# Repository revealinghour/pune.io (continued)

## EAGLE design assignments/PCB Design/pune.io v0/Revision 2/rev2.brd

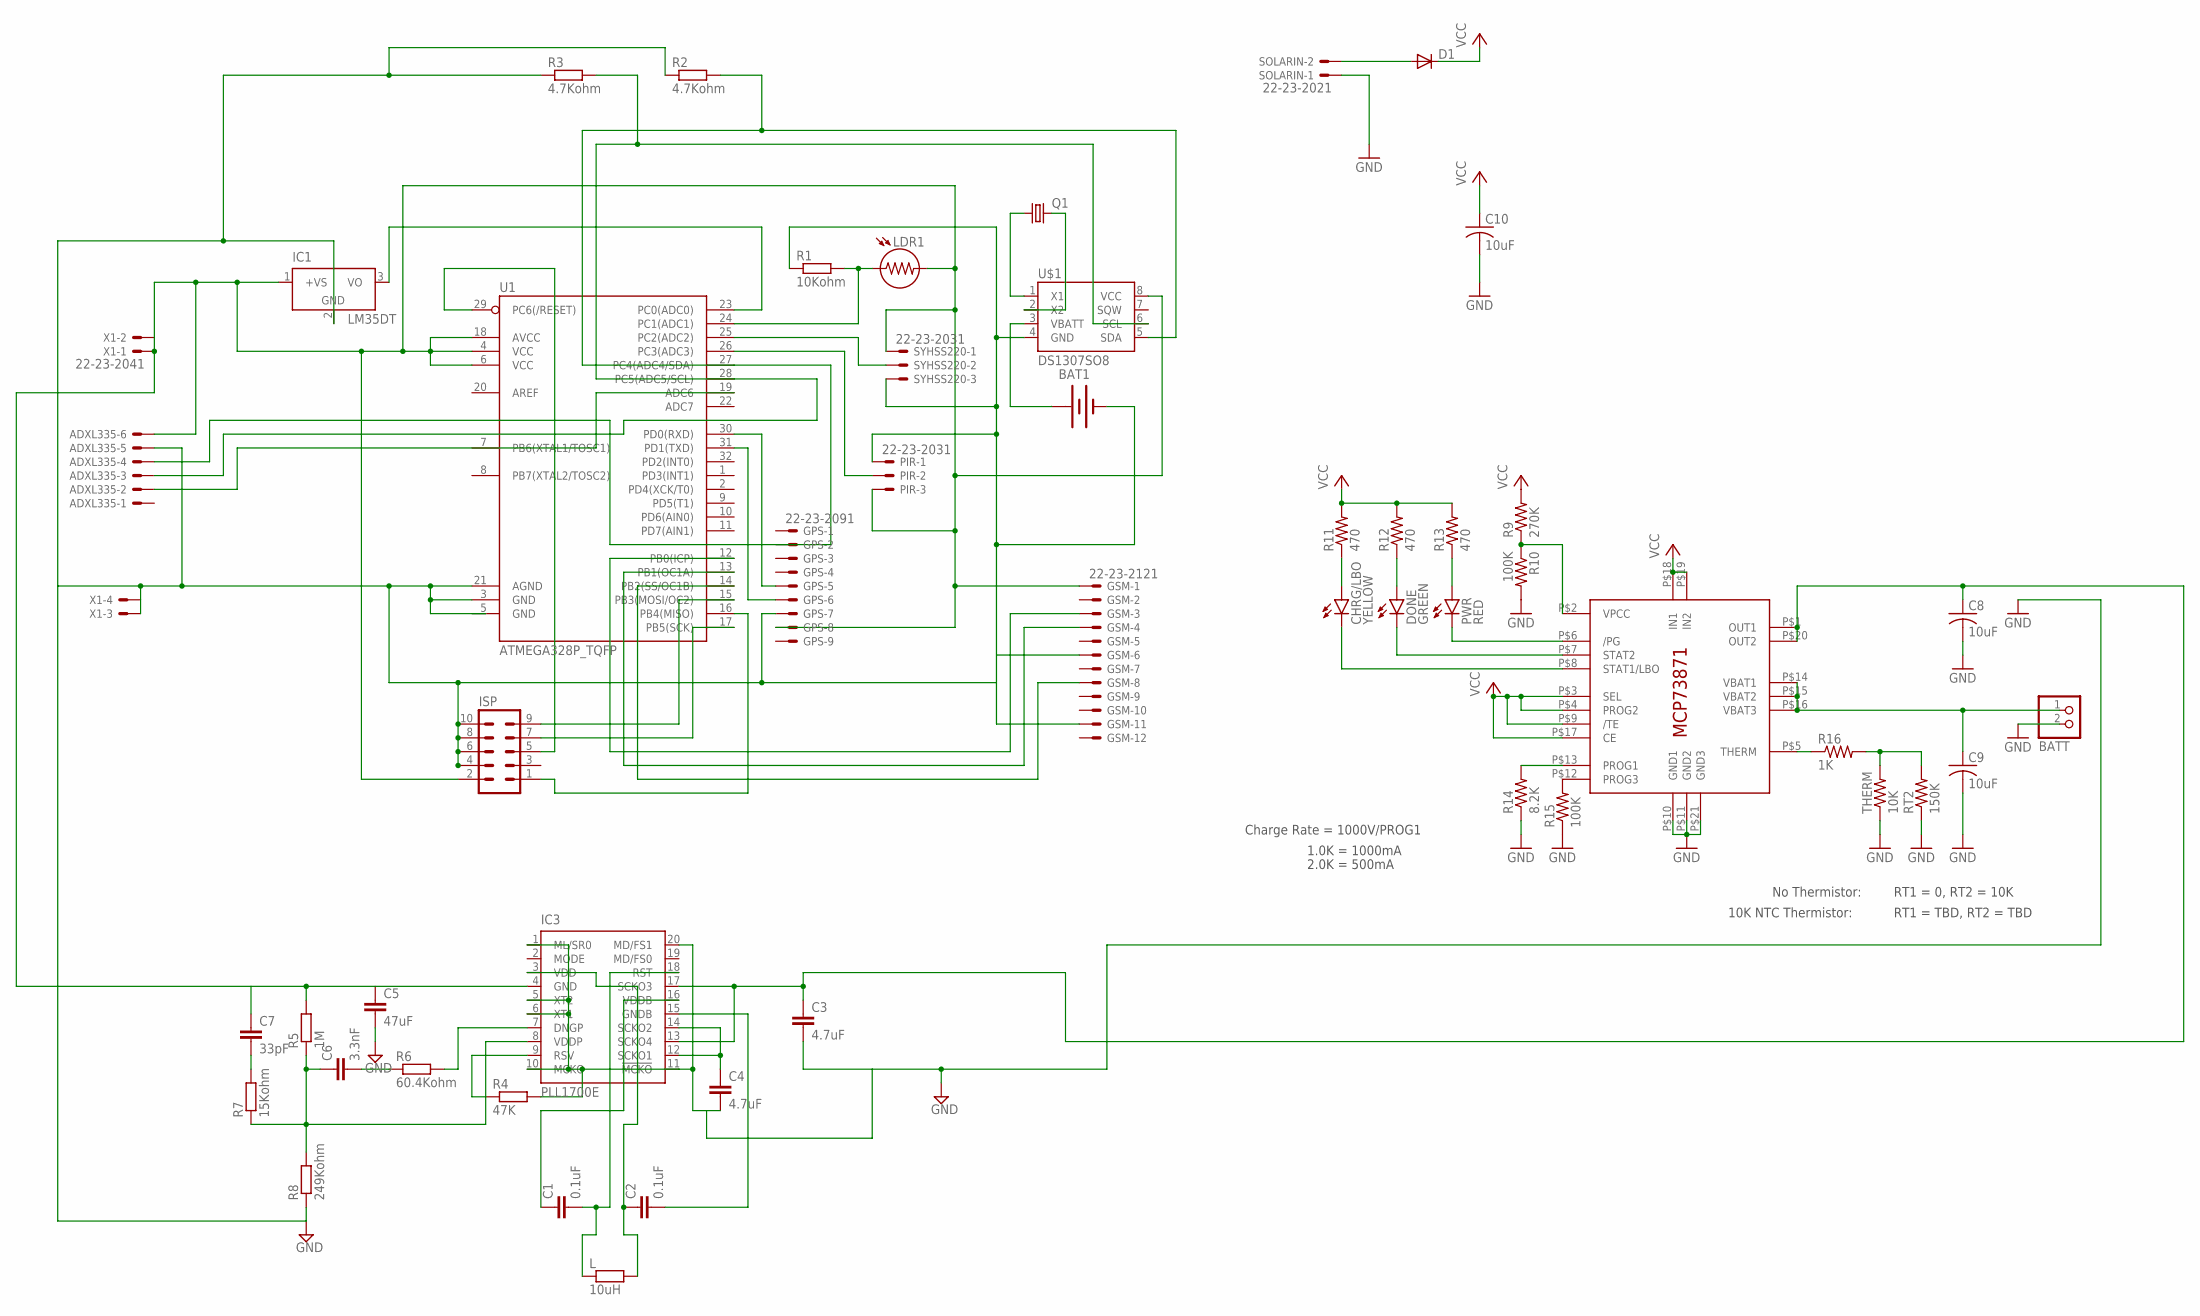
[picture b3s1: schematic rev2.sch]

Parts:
ADXL335: 22-23-2061
BAT1: BATTERY20PTH; BATTCOM_20MM_PTH
BATT: JST_2PIN-SMT-RA; JST-PH-2-SMT-RA
C1, C2: 0.1uF; 0402-CAP
C3, C4: 4.7uF; 0603-CAP
C5: 47uF; 0603-CAP
C6: 3.3nF; 0603-CAP
C7: 33pF; 0603-CAP
C8, C9, C10: 10uF; C0805K
CHRG/LBO: YELLOW; LED-1206
D1: DIODEPTH; DIODE-1N4001
DONE: GREEN; LED-1206
GPS: 22-23-2091
GSM: 22-23-2121
IC1: LM35DT; TO220V
IC2: MCP73871; QFN20_4MM
IC3: PLL1700E; SSOP20
ISP: ML10
L: 10uH; R0207/4
LDR1: LDR5MM; LDR338-54C
PIR: 22-23-2031
PWR: RED; LED-1206
Q1: CRYSTALTC26H; TC26H
R1: 10Kohm; M1206
R2, R3: 4.7Kohm; M1206
R4: 47K; M3216
R5: 1M; M3216
R6: 60.4Kohm; M3216
R7: 15Kohm; M1206
R8: 249Kohm; M1206
R9: 270K; R0805
R10, R15: 100K; R0805
R11, R12, R13: 470; 0603-RES
R14: 8.2K; 0603-RES
R16: 1K; M0805
RT2: 150K; M0805
SOLARIN: 22-23-2021
SYHSS220: 22-23-2031
THERM: 10K; 0805-THM
U1: ATMEGA328P_TQFP; TQFP32-08
U$1: DS1307SO8; SO08
X1: 22-23-2041

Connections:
BATT: BATT.1 (2), C9.1, IC2.P$14 (VBAT1), IC2.P$15 (VBAT2), IC2.P$16 (VBAT3)
GND: ADXL335.5, BAT1.2 (-), BATT.2 (1), C3.2, C4.2, C5.2, C8.2, C9.2, C10.2, GPS.7, GSM.6, GSM.11, IC1.2 (GND), IC2.P$10 (GND1), IC2.P$11 (GND2), IC2.P$21 (GND3), IC3.1 (ML/SR0), IC3.5 (XT2), IC3.6 (XT1), IC3.10 (MCKO), IC3.11 (!MCKO), IC3.20 (MD/FS1), ISP.4, ISP.6, ISP.8, ISP.10, PIR.1, R1.1, R2.1, R3.1, R4.2, R8.1, R10.2, R14.1, R15.1, RT2.1, SOLARIN.1, SYHSS220.3, THERM.1, U1.3 (GND), U1.21 (AGND), U$1.4 (GND), X1.3, X1.4
unnamed: GPS.5, U1.30 (PD0(RXD))
unnamed: IC1.3 (VO), U1.23 (PC0(ADC0))
unnamed: LDR1.1, R1.2, U1.24 (PC1(ADC1))
unnamed: GPS.6, U1.31 (PD1(TXD))
unnamed: SYHSS220.2, U1.25 (PC2(ADC2))
unnamed: PIR.2, U1.26 (PC3(ADC3))
unnamed: ADXL335.2, U1.19 (ADC6)
unnamed: ADXL335.3, R3.2, U1.28 (PC5(ADC5/SCL)), U$1.6 (SCL)
unnamed: GSM.3, U1.12 (PB0(ICP))
unnamed: Q1.1, U$1.1 (X1)
unnamed: Q1.2, U$1.2 (X2)
unnamed: GSM.4, U1.13 (PB1(OC1A))
unnamed: BAT1.1 (+), U$1.3 (VBATT)
unnamed: GSM.8, U1.14 (PB2(SS/OC1B))
unnamed: IC2.P$2 (VPCC), R9.1, R10.1
unnamed: IC2.P$6 (/PG), PWR.C
unnamed: ISP.1, U1.16 (PB4(MISO))
unnamed: ISP.5, U1.29 (PC6(/RESET))
unnamed: ISP.7, U1.17 (PB5(SCK))
unnamed: ISP.9, U1.15 (PB3(MOSI/OC2))
unnamed: DONE.C, IC2.P$7 (STAT2)
unnamed: CHRG/LBO.C, IC2.P$8 (STAT1/LBO)
unnamed: C1.1, IC3.16 (VDDB)
unnamed: CHRG/LBO.A, R11.1
unnamed: DONE.A, R12.1
unnamed: C2.2, IC3.15 (GNDB)
unnamed: PWR.A, R13.1
unnamed: IC2.P$12 (PROG3), R15.2
unnamed: C1.2, IC3.18 (RST), L.1
unnamed: C2.1, IC3.3 (VDD), L.2
unnamed: ADXL335.6, C5.1, C7.1, GPS.8, GSM.1, IC1.1 (+VS), IC3.4 (GND), ISP.2, LDR1.2, PIR.3, R5.2, SYHSS220.1, U1.4 (VCC), U1.6 (VCC), U1.18 (AVCC), U$1.8 (VCC), X1.1, X1.2
unnamed: C6.1, IC3.8 (VDDP), R5.1, R7.1, R8.2
unnamed: C6.2, R6.1
unnamed: IC3.7 (DNGP), R6.2
unnamed: ADXL335.4, R2.2, U1.27 (PC4(ADC4/SDA)), U$1.5 (SDA)
unnamed: C7.2, R7.2
unnamed: C4.1, IC3.12 (SCKO1), IC3.14 (SCKO2)
unnamed: IC3.9 (RSV), R4.1
unnamed: IC2.P$13 (PROG1), R14.2
unnamed: IC2.P$5 (THERM), R16.1
unnamed: R16.2, RT2.2, THERM.2
unnamed: D1.A, SOLARIN.2
OUT: C3.1, C8.1, IC2.P$1 (OUT1), IC2.P$20 (OUT2), IC3.13 (SCKO4), IC3.17 (SCKO3)
VCC: C10.1, D1.C, IC2.P$3 (SEL), IC2.P$4 (PROG2), IC2.P$9 (/TE), IC2.P$17 (CE), IC2.P$18 (IN1), IC2.P$19 (IN2), R9.2, R11.2, R12.2, R13.2

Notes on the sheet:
Charge Rate = 1000V/PROG1
1.0K = 1000mA
2.0K = 500mA
No Thermistor:
10K NTC Thermistor:
RT1 = 0, RT2 = 10K
RT1 = TBD, RT2 = TBD

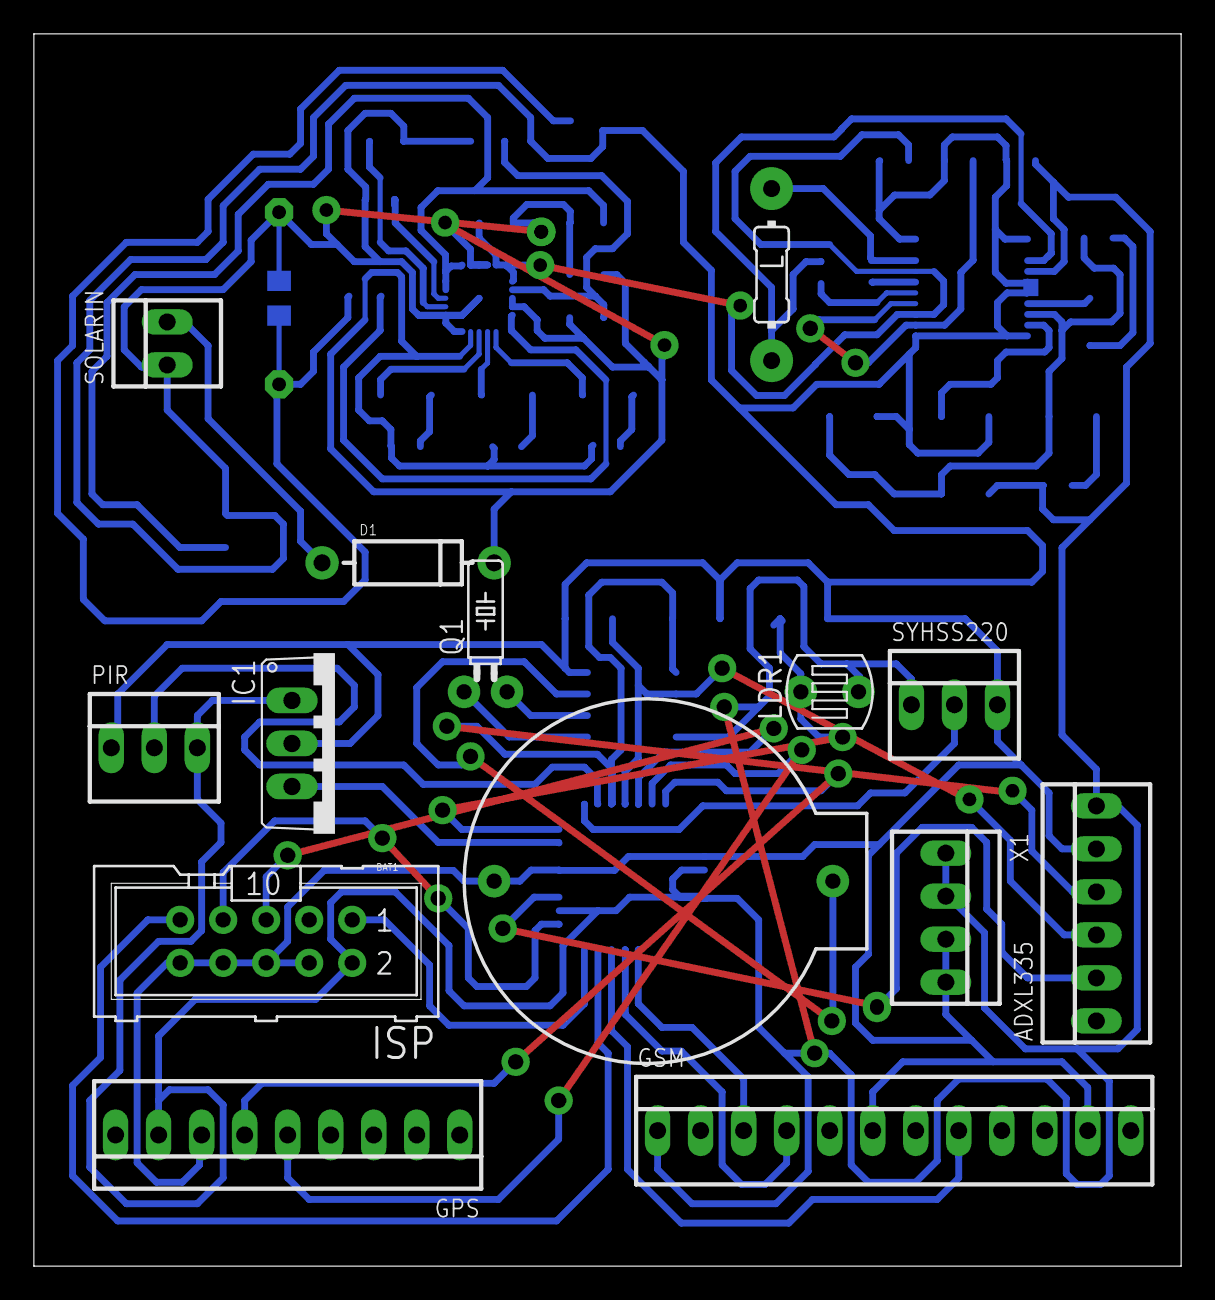
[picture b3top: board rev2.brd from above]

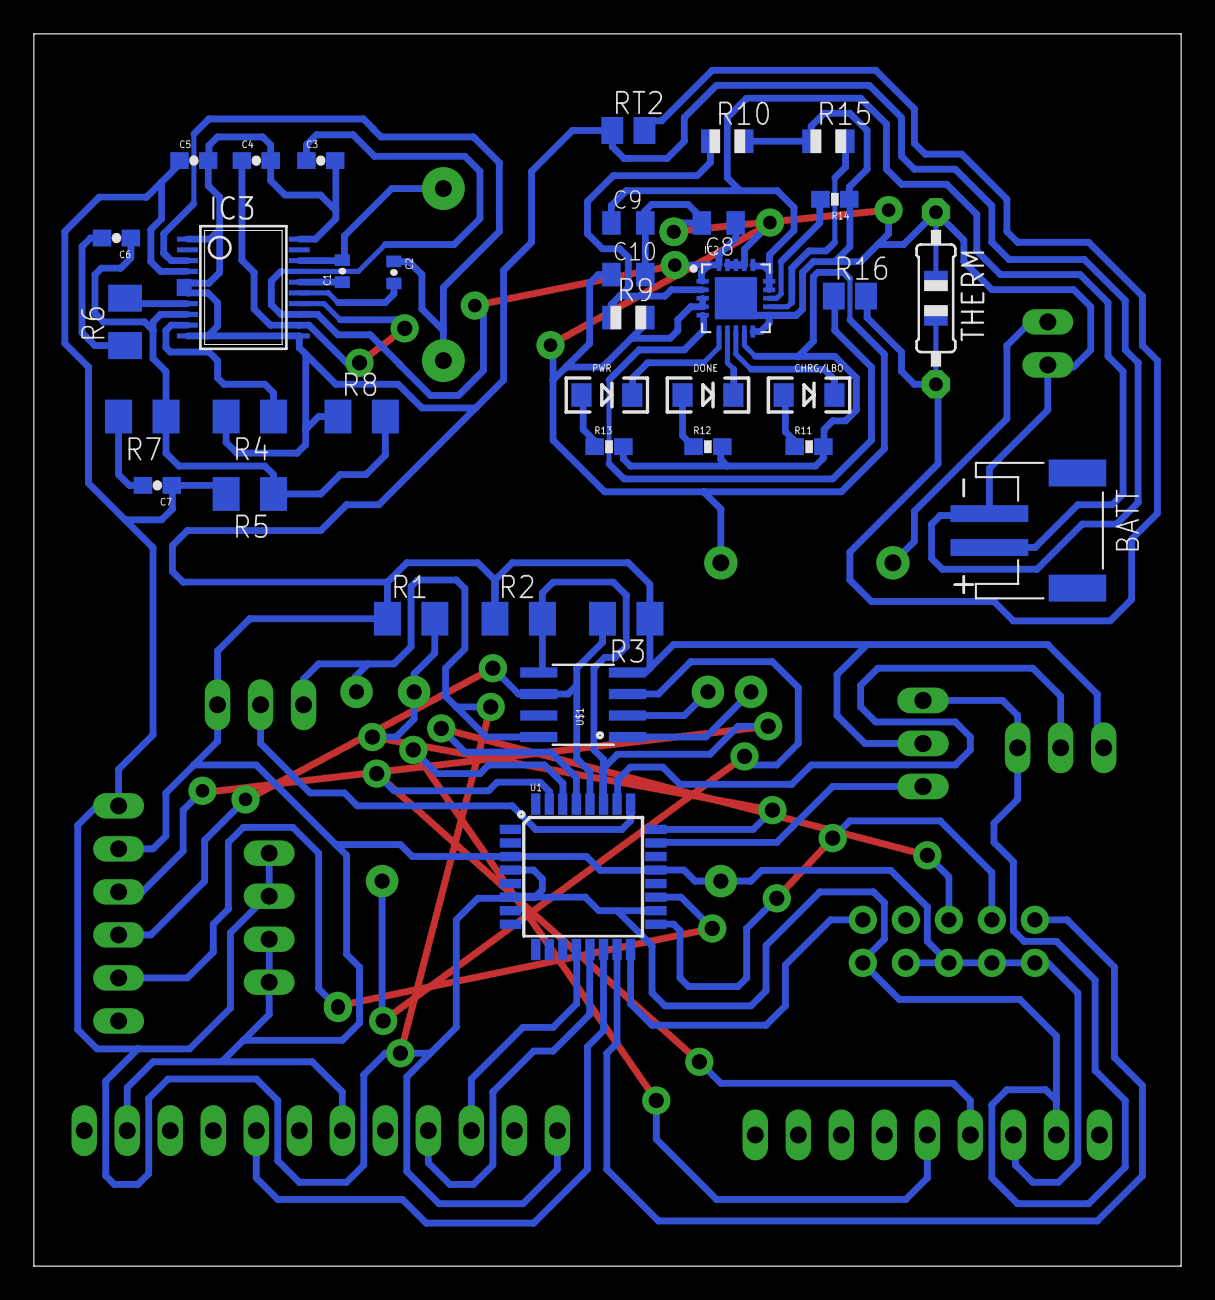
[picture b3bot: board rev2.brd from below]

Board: 2 copper layers, 67.7 x 72.8 mm, 50 parts (36 on the bottom side), 46 nets.

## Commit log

2014-08-25 Create jsonparsing
    assignment to parse a json file from a local folder and diaplay in the terminal.
2014-08-25 Create jsonparsingurl
    assignment to download a json file and parse it.
2014-08-25 Create lcdserial
    serial communication using arduino serial monitor.
2014-08-25 Rename python-code-for-download-a-data-stream-learning-import-sys-json-from-pprint-import-pprint-json_data-open/home/mithilesh/Downloads/jsonparsing to jsonparsing.py
2014-08-25 Rename python-code-for-download-a-data-stream-learning-import-sys-json-from-pprint-import-pprint-json_data-open/home/mithilesh/Downloads/jsonparsingurl to jsonparsingurl.py
2014-08-25 Rename python-code-for-download-a-data-stream-learning-import-sys-json-from-pprint-import-pprint-json_data-open/home/mithilesh/Downloads/lcdserial to lcdserial.ino
2014-09-09 Create twittertry1.py
    In the terminal, it says authentication error
2014-09-09 Create twitertry2.py
    It gives the following error
    Enter user name mithilesh_d27
    Traceback (most recent call last):
    File "twitn.py", line 5, in <module>
    statuses = api.GetUserTimeline(input)
    File "build/bdist.linux-x86_64/egg/twitter/api.py", line 628, in GetUserTimeline
2014-09-09 Create twittertry3.py
    It gives the following error
    Traceback (most recent call last):
    File "twittnew.py", line 4, in <module>
    statuses=api.GetPublicTimeline()
    AttributeError: 'Api' object has no attribute 'GetPublicTimeline'
2014-09-25 Create Downloaded Tweets
2014-12-03 Reorganize, add folder for sensors
2014-12-09 Added an lm35 datasheet
2014-12-11 All the sensors and other IC datasheets revised
2014-12-31 codes for pushing data
2015-01-03 Schematic File
2015-01-03 Changes to the schematic
2015-01-05 Schematic and Board
2015-01-08 Added power supply and ADXL335 in the PCB design
2015-01-08 Documentation for the API
2015-01-10 Revision 2 for the PCB design
2015-01-12 Revisions for PCB design and datasheet additions
2015-01-14 Minor changes
2015-02-02 Move github pages to this repo
2015-02-02 Move schematics and design files to hardware/
    Remove old assignments
2015-02-02 Remove readme
2015-02-19 Redesigned the landing page and included API documentation.
2015-02-20 Redesigning of PCB with upper and lower board, pune.io v1
2015-02-27 Redo footer
2016-05-30 Remove CNAME
